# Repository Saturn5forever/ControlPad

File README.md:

# ControlPad
My Hackpad that controls music and other controls on my computer quickly.

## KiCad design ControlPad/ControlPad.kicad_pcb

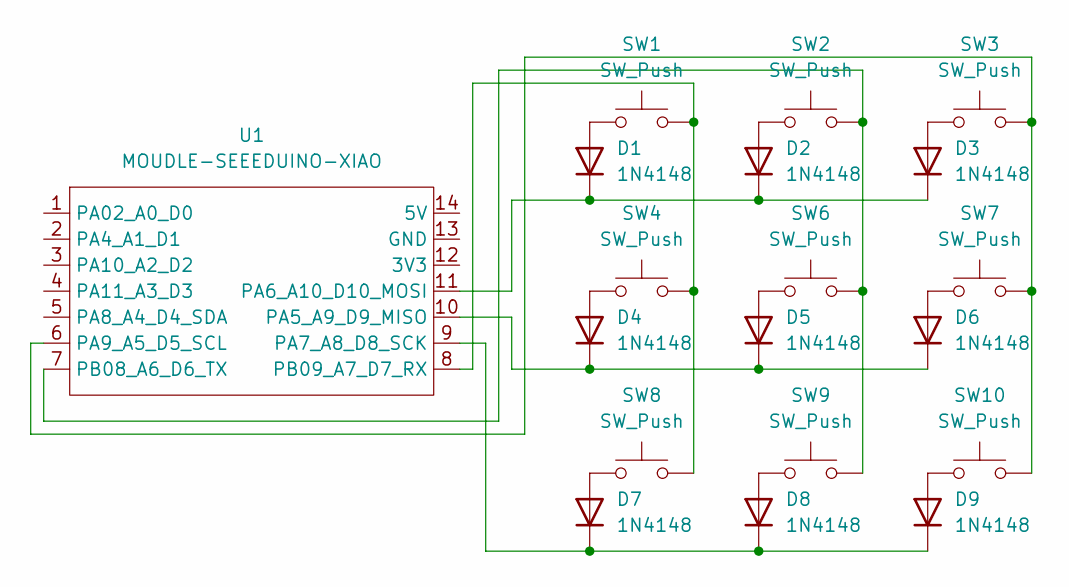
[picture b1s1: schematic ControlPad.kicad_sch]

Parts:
D1, D2, D3, D4, D5, D6, D7, D8, D9: 1N4148; D_DO-35_SOD27_P7.62mm_Horizontal
SW1, SW2, SW3, SW4, SW6, SW7, SW8, SW9, SW10: SW_Push; SW_Cherry_MX_1.00u_PCB
U1: MOUDLE-SEEEDUINO-XIAO; XIAO-Generic-Hybrid-14P-2.54-21X17.8MM

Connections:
unnamed: D1.2 (A), SW1.1
unnamed: D1.1 (K), D2.1 (K), D3.1 (K), U1.11 (PA6_A10_D10_MOSI)
unnamed: D2.2 (A), SW2.1
unnamed: D3.2 (A), SW3.1
unnamed: D4.2 (A), SW4.1
unnamed: D4.1 (K), D5.1 (K), D6.1 (K), U1.10 (PA5_A9_D9_MISO)
unnamed: D5.2 (A), SW6.1
unnamed: D6.2 (A), SW7.1
unnamed: D7.2 (A), SW8.1
unnamed: D7.1 (K), D8.1 (K), D9.1 (K), U1.9 (PA7_A8_D8_SCK)
unnamed: D8.2 (A), SW9.1
unnamed: D9.2 (A), SW10.1
unnamed: SW3.2, SW7.2, SW10.2, U1.6 (PA9_A5_D5_SCL)
unnamed: SW2.2, SW6.2, SW9.2, U1.7 (PB08_A6_D6_TX)
unnamed: SW1.2, SW4.2, SW8.2, U1.8 (PB09_A7_D7_RX)

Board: 2 copper layers, 19 parts (1 on the bottom side), 15 nets, no tracks yet.

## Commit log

2026-06-11 PCB Schematic and Layout design
2026-06-12 Traces Routing V1
2026-06-12 Traces Routing V2
2026-06-12 Silk Screen Art and PCB Boader
    I added a ControlPad Logo and Hack Club logo to the silkscreen of the PCB and I added a boarder.
2026-06-12 Organizing Art
